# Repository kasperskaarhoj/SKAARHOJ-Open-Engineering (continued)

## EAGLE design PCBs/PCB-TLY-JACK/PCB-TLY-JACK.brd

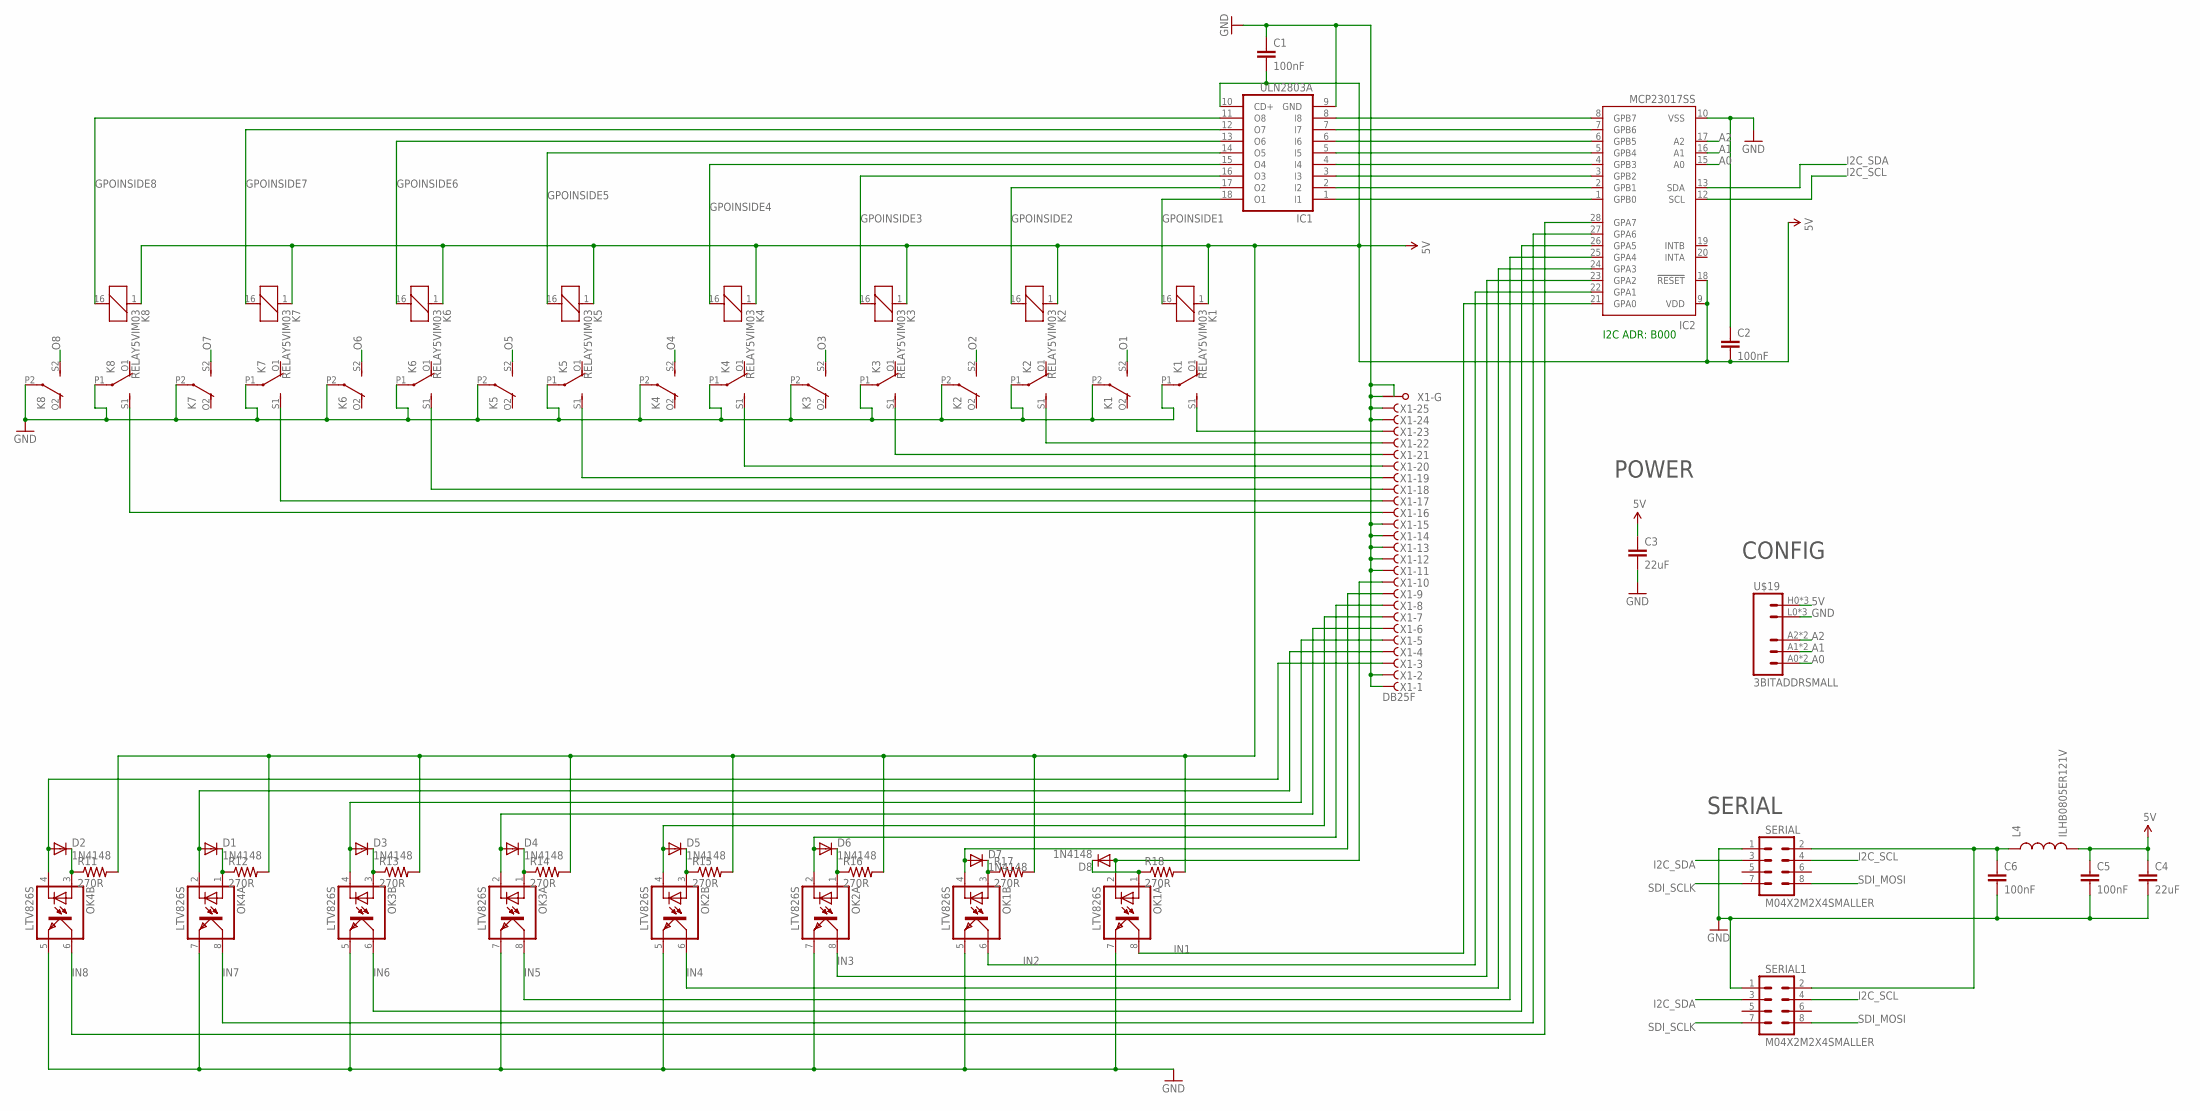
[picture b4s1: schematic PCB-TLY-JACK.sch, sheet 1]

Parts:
C1, C2, C5, C6: 100nF; 0603-CAP
C3, C4: 22uF; 0805
D1, D2, D3, D4, D5, D6, D7, D8: 1N4148; SOD-323
IC1: ULN2803A; SO18W
IC2: MCP23017SS; SSOP28
K1, K2, K3, K4, K5, K6, K7, K8: RELAY5VIM03; DS2Y
L4: ILHB0805ER121V; 0805
OK1, OK2, OK3, OK4: LTV826S; DIL8-SMD
R11, R12, R13, R14, R15, R16, R17, R18: 270R; 0603-RES
SERIAL, SERIAL1: M04X2M2X4SMALLER; M2X4SMALLER
U$19: 3BITADDRSMALL; 3BITADDR_SMALL
X1: DB25F; F25HP

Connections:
5V: C1.2, C2.2, C3.1, C4.1, C5.1, IC1.10 (CD+), IC2.9 (VDD), IC2.18 (!RESET), K1.1, K2.1, K3.1, K4.1, K5.1, K6.1, K7.1, K8.1, L4.2, R11.2, R12.2, R13.2, R14.2, R15.2, R16.2, R17.2, R18.2, U$19.H0 (VCC), U$19.H1 (VCC), U$19.H2 (VCC)
A0: IC2.15 (A0), U$19.A0, U$19.AS0 (A0)
A1: IC2.16 (A1), U$19.A1, U$19.AS1 (A1)
A2: IC2.17 (A2), U$19.A2, U$19.AS2 (A2)
GND: C1.1, C2.1, C3.2, C4.2, C5.2, C6.2, IC1.9 (GND), IC2.10 (VSS), K1.P1, K1.P2, K2.P1, K2.P2, K3.P1, K3.P2, K4.P1, K4.P2, K5.P1, K5.P2, K6.P1, K6.P2, K7.P1, K7.P2, K8.P1, K8.P2, OK1.5 (EMIT), OK1.7 (EMIT), OK2.5 (EMIT), OK2.7 (EMIT), OK3.5 (EMIT), OK3.7 (EMIT), OK4.5 (EMIT), OK4.7 (EMIT), SERIAL.1, SERIAL1.1, U$19.L0 (GND), U$19.L1 (GND), U$19.L2 (GND), X1.1 (F), X1.2 (F), X1.11 (F), X1.12 (F), X1.13 (F), X1.14 (F), X1.15 (F), X1.24 (F), X1.25 (F), X1.G1, X1.G2
GPOINSIDE1: IC1.18 (O1), K1.16 (2)
GPOINSIDE2: IC1.17 (O2), K2.16 (2)
GPOINSIDE3: IC1.16 (O3), K3.16 (2)
GPOINSIDE4: IC1.15 (O4), K4.16 (2)
GPOINSIDE5: IC1.14 (O5), K5.16 (2)
GPOINSIDE6: IC1.13 (O6), K6.16 (2)
GPOINSIDE7: IC1.12 (O7), K7.16 (2)
GPOINSIDE8: IC1.11 (O8), K8.16 (2)
I2C_SCL: IC2.12 (SCL), SERIAL.4, SERIAL1.4
I2C_SDA: IC2.13 (SDA), SERIAL.3, SERIAL1.3
IN1: IC2.21 (GPA0), OK1.8 (COL)
IN2: IC2.22 (GPA1), OK1.6 (COL)
IN3: IC2.23 (GPA2), OK2.8 (COL)
IN4: IC2.24 (GPA3), OK2.6 (COL)
IN5: IC2.25 (GPA4), OK3.8 (COL)
IN6: IC2.26 (GPA5), OK3.6 (COL)
IN7: IC2.27 (GPA6), OK4.8 (COL)
IN8: IC2.28 (GPA7), OK4.6 (COL)
unnamed: K1.S1 (S), X1.23 (F)
unnamed: C6.1, L4.1, SERIAL.2, SERIAL1.2
unnamed: IC1.1 (I1), IC2.1 (GPB0)
unnamed: K2.S1 (S), X1.22 (F)
unnamed: K3.S1 (S), X1.21 (F)
unnamed: D2.1 (C), OK4.3 (A), R11.1
unnamed: K4.S1 (S), X1.20 (F)
unnamed: D1.1 (C), OK4.1 (A), R12.1
unnamed: D3.1 (C), OK3.3 (A), R13.1
unnamed: D4.1 (C), OK3.1 (A), R14.1
unnamed: K5.S1 (S), X1.19 (F)
unnamed: D5.1 (C), OK2.3 (A), R15.1
unnamed: D6.1 (C), OK2.1 (A), R16.1
unnamed: D7.1 (C), OK1.3 (A), R17.1
unnamed: K6.S1 (S), X1.18 (F)
unnamed: D8.1 (C), OK1.1 (A), R18.1
unnamed: K7.S1 (S), X1.17 (F)
unnamed: K8.S1 (S), X1.16 (F)
unnamed: IC1.2 (I2), IC2.2 (GPB1)
unnamed: IC1.3 (I3), IC2.3 (GPB2)
unnamed: IC1.4 (I4), IC2.4 (GPB3)
unnamed: IC1.5 (I5), IC2.5 (GPB4)
unnamed: IC1.6 (I6), IC2.6 (GPB5)
unnamed: IC1.7 (I7), IC2.7 (GPB6)
unnamed: IC1.8 (I8), IC2.8 (GPB7)
unnamed: D8.2 (A), OK1.2 (C), X1.10 (F)
unnamed: D4.2 (A), OK3.2 (C), X1.6 (F)
unnamed: D7.2 (A), OK1.4 (C), X1.9 (F)
unnamed: D6.2 (A), OK2.2 (C), X1.8 (F)
unnamed: D5.2 (A), OK2.4 (C), X1.7 (F)
unnamed: D3.2 (A), OK3.4 (C), X1.5 (F)
unnamed: D1.2 (A), OK4.2 (C), X1.4 (F)
unnamed: D2.2 (A), OK4.4 (C), X1.3 (F)
O1: K1.S2 (S)
O2: K2.S2 (S)
O3: K3.S2 (S)
O4: K4.S2 (S)
O5: K5.S2 (S)
O6: K6.S2 (S)
O7: K7.S2 (S)
O8: K8.S2 (S)
SDI_MOSI: SERIAL.8, SERIAL1.8
SDI_SCLK: SERIAL.7, SERIAL1.7

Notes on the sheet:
I2C ADR: B000
SERIAL
POWER
CONFIG

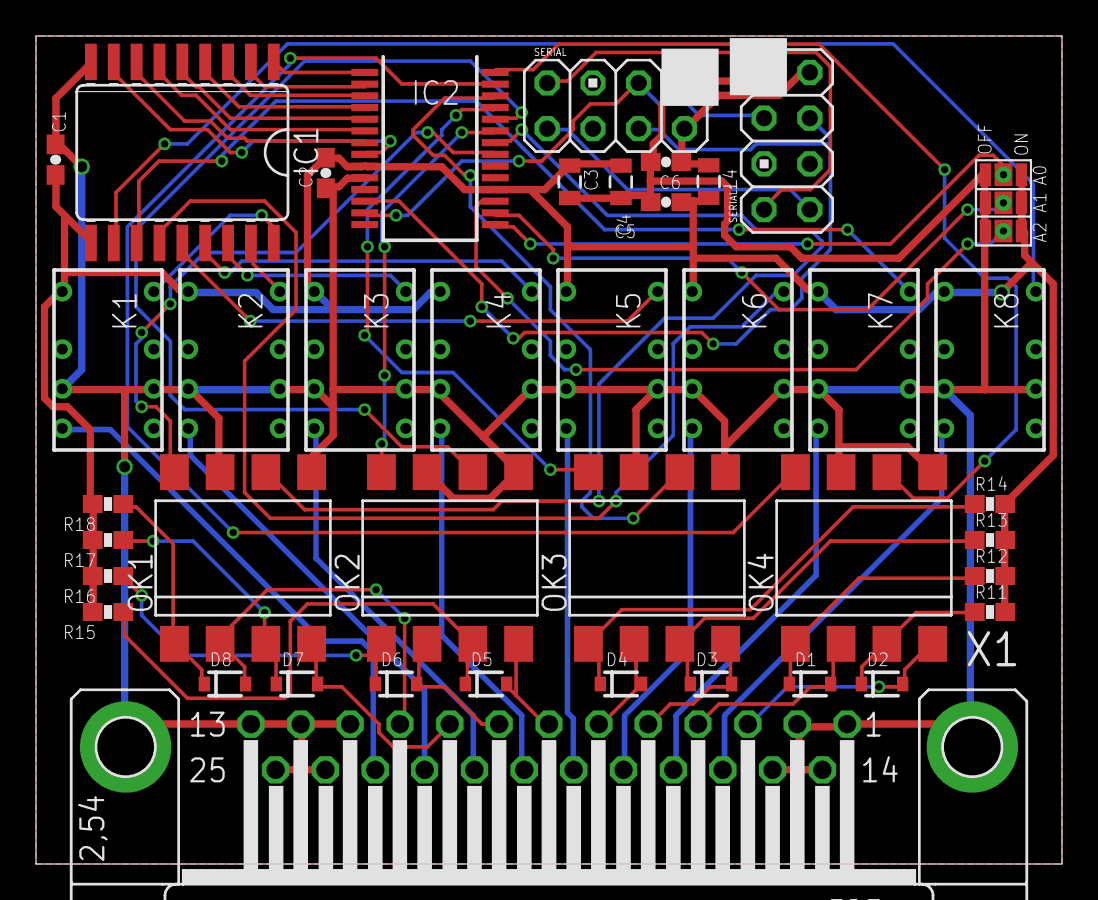
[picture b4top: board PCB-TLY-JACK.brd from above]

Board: 2 copper layers, 57.0 x 46.0 mm, 41 parts (0 on the bottom side), 58 nets.

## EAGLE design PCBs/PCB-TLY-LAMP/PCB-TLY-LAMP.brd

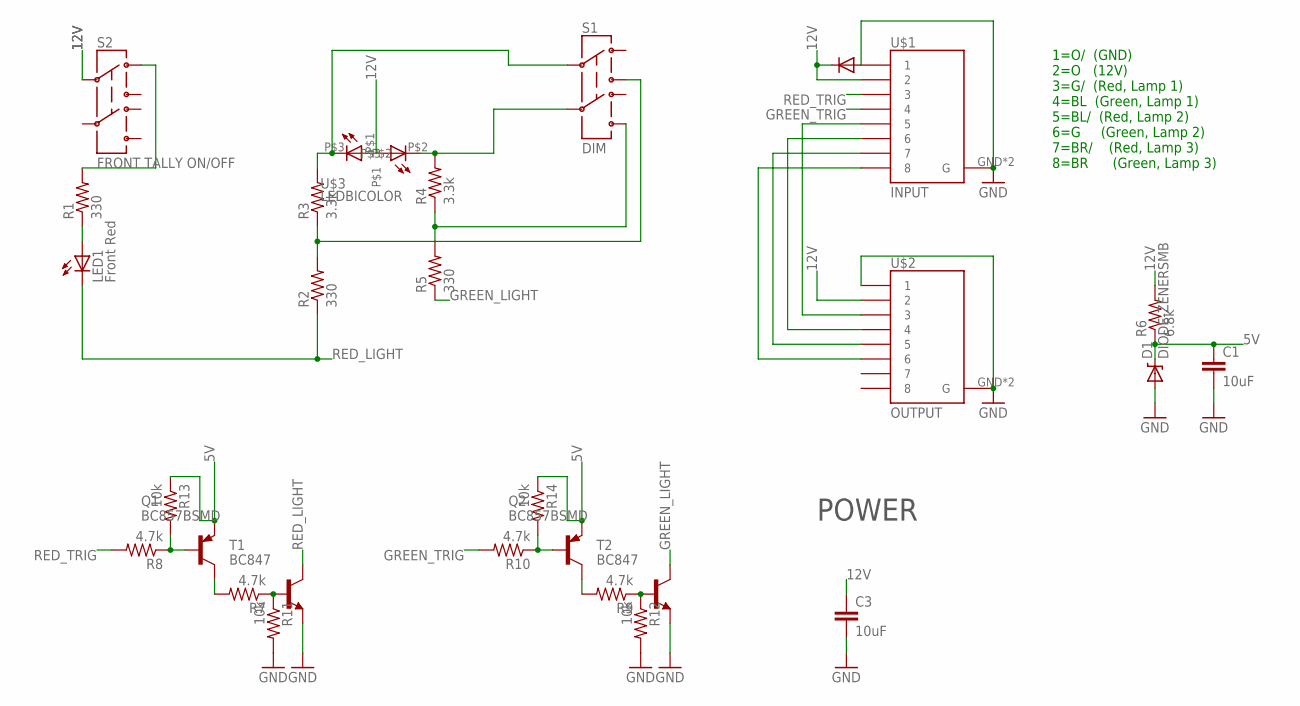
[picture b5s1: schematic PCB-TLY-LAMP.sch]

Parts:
C1, C3: 10uF; 0805
D1: DIODE-ZENERSMB; SMB-DIODE
LED1: Front Red; LED20
Q1, Q2: BC857BSMD; SOT23-BEC
R1, R2, R5: 330; 0603-RES
R3, R4: 3.3k; 0603-RES
R6: 6.8k; 0603-RES
R7, R8, R9, R10: 4.7k; 0603-RES
R11, R12, R13, R14: 10k; 0603-RES
S1: DIM; TECONNECTIVITY-DPDT
S2: FRONT TALLY ON/OFF; TECONNECTIVITY-DPDT
T1, T2: BC847; SOT23
U$1: INPUT; RJ45-8_GND
U$2: OUTPUT; RJ45-8_GND
U$3: LEDBICOLOR

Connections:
5V: C1.1, D1.C, Q1.E, Q2.E, R6.1, R13.1, R14.1
12V: C3.1, R6.2, S2.P$2 (2), U$1.2, U$2.2, U$3.P$1
GND: C1.2, C3.2, D1.A, R11.2, R12.2, T1.2 (E), T2.2 (E), U$1.1, U$1.GND (G), U$1.GND1 (G), U$2.1, U$2.GND (G), U$2.GND1 (G)
GREEN_LIGHT: R5.1, T2.3 (C)
GREEN_TRIG: R10.2, U$1.4
unnamed: R1.2, S2.P$1 (1)
unnamed: LED1.P$1 (A), R1.1
unnamed: R2.2, R3.1, S1.P$3 (3)
unnamed: R4.1, R5.2, S1.P$6 (6)
unnamed: R4.2, S1.P$5 (5), U$3.P$2
unnamed: R3.2, S1.P$2 (2), U$3.P$3
unnamed: U$1.5, U$2.3
unnamed: U$1.6, U$2.4
unnamed: R7.1, R11.1, T1.1 (B)
unnamed: Q1.C, R7.2
unnamed: U$1.7, U$2.5
unnamed: U$1.8, U$2.6
unnamed: R9.1, R12.1, T2.1 (B)
unnamed: Q2.C, R9.2
unnamed: Q2.B, R10.1, R14.2
unnamed: Q1.B, R8.1, R13.2
RED_LIGHT: LED1.P$2 (C), R2.1, T1.3 (C)
RED_TRIG: R8.2, U$1.3

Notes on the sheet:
POWER
1=O/ (GND) 2=O (12V) 3=G/ (Red, Lamp 1) 4=BL (Green, Lamp 1) 5=BL/ (Red, Lamp 2) 6=G (Green, Lamp 2) 7=BR/ (Red, Lamp 3) 8=BR (Green, Lamp 3)

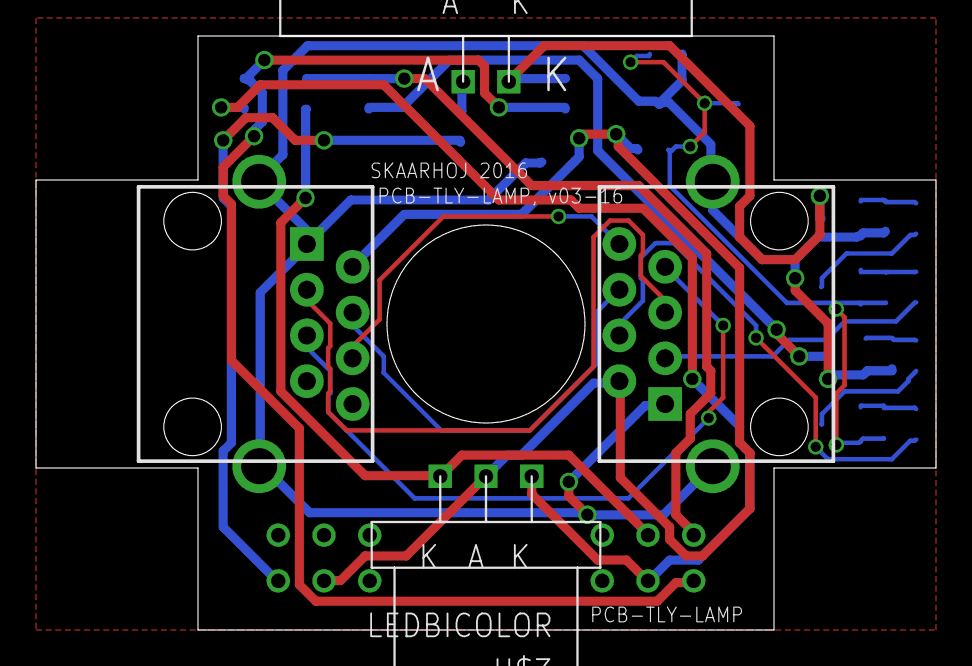
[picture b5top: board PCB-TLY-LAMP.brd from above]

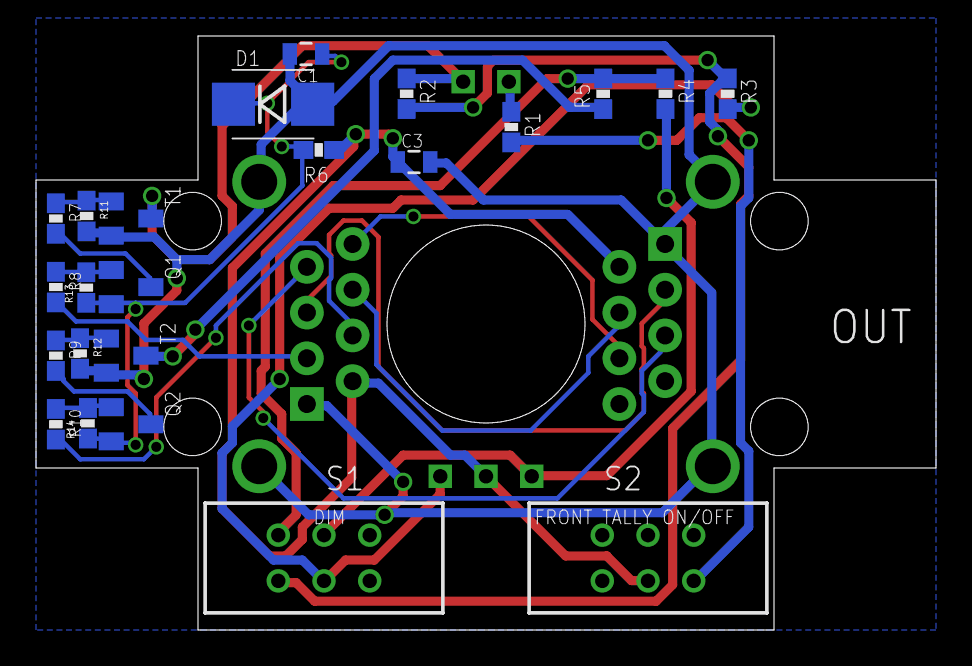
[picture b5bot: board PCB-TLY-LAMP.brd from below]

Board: 2 copper layers, 50.0 x 33.0 mm, 27 parts (23 on the bottom side), 23 nets.

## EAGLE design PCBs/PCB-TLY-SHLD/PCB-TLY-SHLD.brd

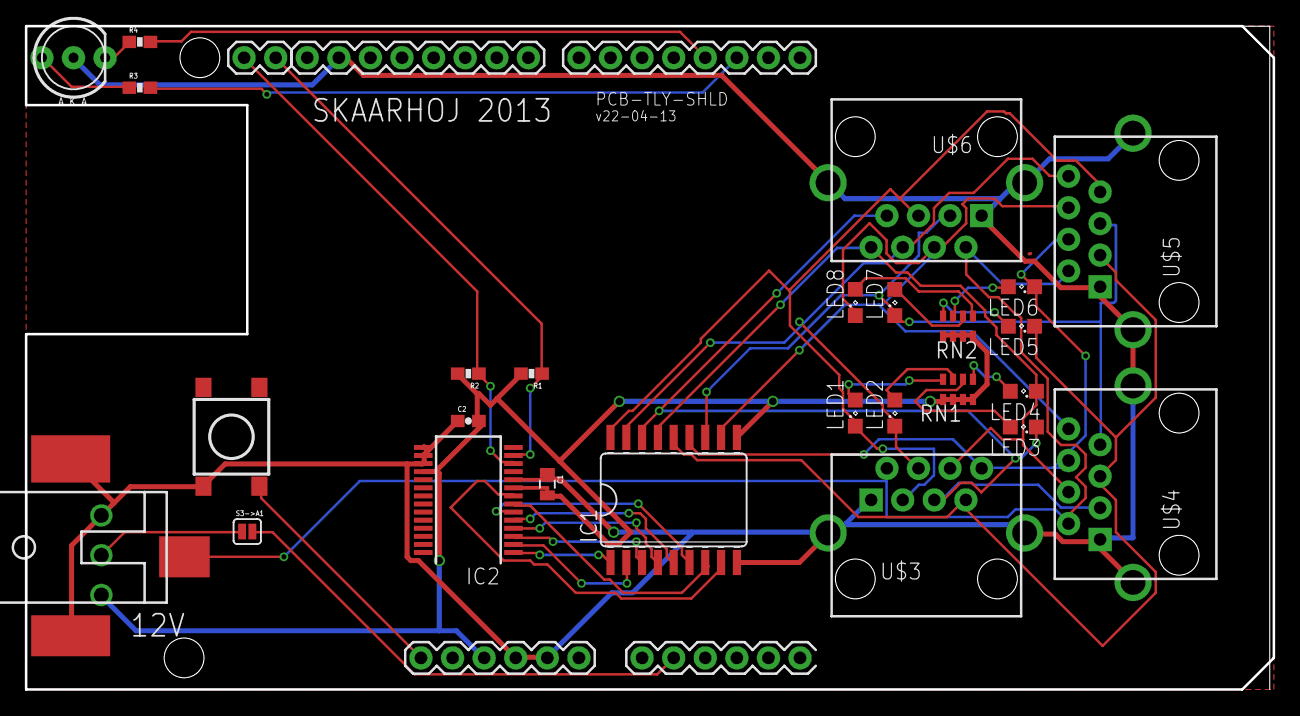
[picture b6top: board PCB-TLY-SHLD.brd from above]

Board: 2 copper layers, 100.3 x 53.3 mm, 29 parts (1 on the bottom side), 36 nets.

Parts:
C1: 100nF; 0805
C2: 100nF; 0603-CAP
GND: ARDUINO_SHIELD; ARDUINO_BOXSHIELD_NOHOLES
IC1: ULN2803A; SO18W
IC2: MCP23017SS; SSOP28
J1: POWER_JACK_SMD
JP4: 1X02
LED1, LED2, LED3, LED4, LED5, LED6, LED7, LED8: SML0805
R1, R2: 1K5; 0603-RES
R3, R4: 270; 0603-RES
RN1, RN2: 220; CAY16_HAND
S1: SWITCH-MOMENTARY-2; TACTILE_SWITCH_TALL
S3: CFG; TECONNECTIVITY-DPST
S3->A1: SOLDERJUMPERNC; SJ_2S
U$3: Tally 1-2-3; RJ45-8_GND
U$4: Tally 2-3-4; RJ45-8_GND
U$5: Tally 3-4-1; RJ45-8_GND
U$6: Tally 4-1-2; RJ45-8_GND
U$7: LEDBICOLOR-AKA; LED5MM-BICOLOR

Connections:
5V: C1.2, C2.2, GND.5V@0, IC1.10, IC2.9, IC2.18, R1.2, R2.2, RN1.1, RN1.2, RN1.3, RN1.4, RN2.1, RN2.2, RN2.3, RN2.4, S3.P$1
A1CFG: GND.A1, S3->A1.2
D2: GND.2, R3.2
D3: GND.3, R4.2
GND: C1.1, C2.1, GND.GND@0, GND.GND@1, GND.GND@4, IC1.9, IC2.10, IC2.15, IC2.16, IC2.17, J1.GND, J1.SHUNT, S1.A2, S3.P$3, U$3.1, U$3.GND, U$3.GND1, U$4.1, U$4.GND, U$4.GND1, U$5.1, U$5.GND, U$5.GND1, U$6.1, U$6.GND, U$6.GND1, U$7.K1
I2C_SCL: IC2.12, JP4.2, R2.1
I2C_SDA: IC2.13, JP4.1, R1.1
unnamed: IC1.18, LED1.C, U$3.3, U$5.7, U$6.5
unnamed: S3.P$2, S3->A1.1
unnamed: J1.PWR, U$3.2, U$4.2, U$5.2, U$6.2
unnamed: IC1.1, IC2.1
unnamed: IC1.17, LED2.C, U$3.4, U$5.8, U$6.6
unnamed: R4.1, U$7.A2
unnamed: R3.1, U$7.A3
unnamed: IC1.16, LED3.C, U$3.5, U$4.3, U$6.7
unnamed: IC1.15, LED4.C, U$3.6, U$4.4, U$6.8
unnamed: IC1.14, LED5.C, U$3.7, U$4.5, U$5.3
unnamed: IC1.13, LED6.C, U$3.8, U$4.6, U$5.4
unnamed: IC1.12, LED7.C, U$4.7, U$5.5, U$6.3
unnamed: IC1.11, LED8.C, U$4.8, U$5.6, U$6.4
unnamed: IC1.2, IC2.2
unnamed: IC1.3, IC2.3
unnamed: IC1.4, IC2.4
unnamed: IC1.5, IC2.5
unnamed: IC1.6, IC2.6
unnamed: IC1.7, IC2.7
unnamed: IC1.8, IC2.8
unnamed: LED1.A, RN1.8
unnamed: LED2.A, RN1.7
unnamed: LED3.A, RN1.6
unnamed: LED4.A, RN1.5
unnamed: LED5.A, RN2.8
unnamed: LED6.A, RN2.7
unnamed: LED7.A, RN2.6
unnamed: LED8.A, RN2.5
RES: GND.RESET, S1.B2

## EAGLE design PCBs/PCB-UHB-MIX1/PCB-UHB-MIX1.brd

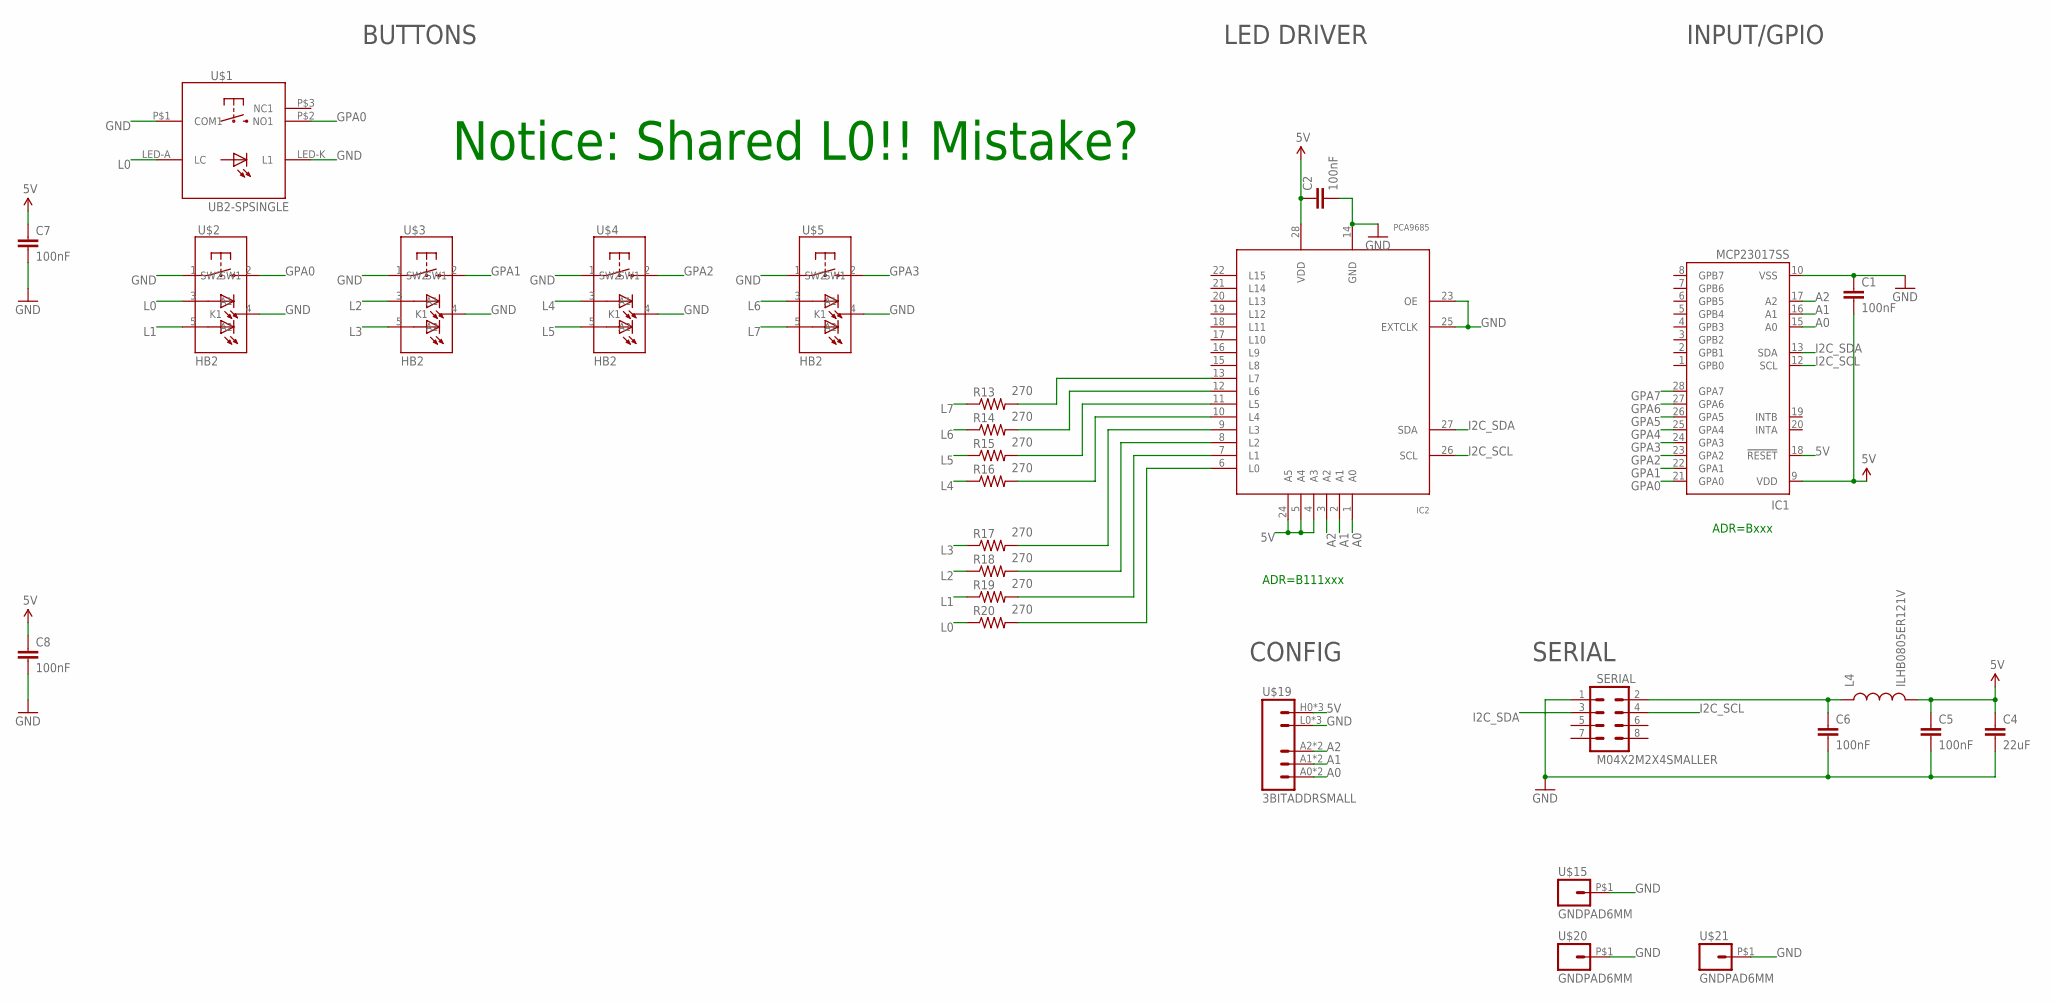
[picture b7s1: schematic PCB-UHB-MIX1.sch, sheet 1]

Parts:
C1, C2, C5, C6, C7, C8: 100nF; 0603-CAP
C4: 22uF; 0805
IC1: MCP23017SS; SSOP28; MPN MCP23017-E/SS
IC2: PCA9685; TSSOP28
L4: ILHB0805ER121V; 0805
R13, R14, R15, R16, R17, R18, R19, R20: 270; 0603-RES
SERIAL: M04X2M2X4SMALLER; M2X4SMALLER
U$1: UB2-SPSINGLE
U$2, U$3, U$4, U$5: HB2
U$15, U$20, U$21: GNDPAD6MM; 3.2MMPAD6MM
U$19: 3BITADDRSMALL; 3BITADDR_SMALL

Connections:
5V: C1.2, C2.1, C4.1, C5.1, C7.1, C8.1, IC1.9 (VDD), IC1.18 (!RESET), IC2.4 (A3), IC2.5 (A4), IC2.24 (A5), IC2.28 (VDD), L4.2, U$19.H0 (VCC), U$19.H1 (VCC), U$19.H2 (VCC)
A0: IC1.15 (A0), IC2.1 (A0), U$19.A0, U$19.AS0 (A0)
A1: IC1.16 (A1), IC2.2 (A1), U$19.A1, U$19.AS1 (A1)
A2: IC1.17 (A2), IC2.3 (A2), U$19.A2, U$19.AS2 (A2)
GND: C1.1, C2.2, C4.2, C5.2, C6.2, C7.2, C8.2, IC1.10 (VSS), IC2.14 (GND), IC2.23 (OE), IC2.25 (EXTCLK), SERIAL.1, U$1.LED-K (L1), U$1.P$1 (COM1), U$2.1 (SW1), U$2.4 (K1), U$3.1 (SW1), U$3.4 (K1), U$4.1 (SW1), U$4.4 (K1), U$5.1 (SW1), U$5.4 (K1), U$15.P$1, U$19.L0 (GND), U$19.L1 (GND), U$19.L2 (GND), U$20.P$1, U$21.P$1
GPA0: IC1.21 (GPA0), U$1.P$2 (NO1), U$2.2 (SW2)
GPA1: IC1.22 (GPA1), U$3.2 (SW2)
GPA2: IC1.23 (GPA2), U$4.2 (SW2)
GPA3: IC1.24 (GPA3), U$5.2 (SW2)
GPA4: IC1.25 (GPA4)
GPA5: IC1.26 (GPA5)
GPA6: IC1.27 (GPA6)
GPA7: IC1.28 (GPA7)
I2C_SCL: IC1.12 (SCL), IC2.26 (SCL), SERIAL.4
I2C_SDA: IC1.13 (SDA), IC2.27 (SDA), SERIAL.3
L0: R20.1, U$1.LED-A (LC), U$2.3 (A1)
L1: R19.1, U$2.5 (A2)
L2: R18.1, U$3.3 (A1)
L3: R17.1, U$3.5 (A2)
L4: R16.1, U$4.3 (A1)
L5: R15.1, U$4.5 (A2)
L6: R14.1, U$5.3 (A1)
L7: R13.1, U$5.5 (A2)
unnamed: C6.1, L4.1, SERIAL.2
unnamed: IC2.13 (L7), R13.2
unnamed: IC2.12 (L6), R14.2
unnamed: IC2.11 (L5), R15.2
unnamed: IC2.10 (L4), R16.2
unnamed: IC2.9 (L3), R17.2
unnamed: IC2.8 (L2), R18.2
unnamed: IC2.7 (L1), R19.2
unnamed: IC2.6 (L0), R20.2

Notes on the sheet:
ADR=B111xxx
ADR=Bxxx
BUTTONS
LED DRIVER
INPUT/GPIO
SERIAL
CONFIG
Notice: Shared L0!! Mistake?

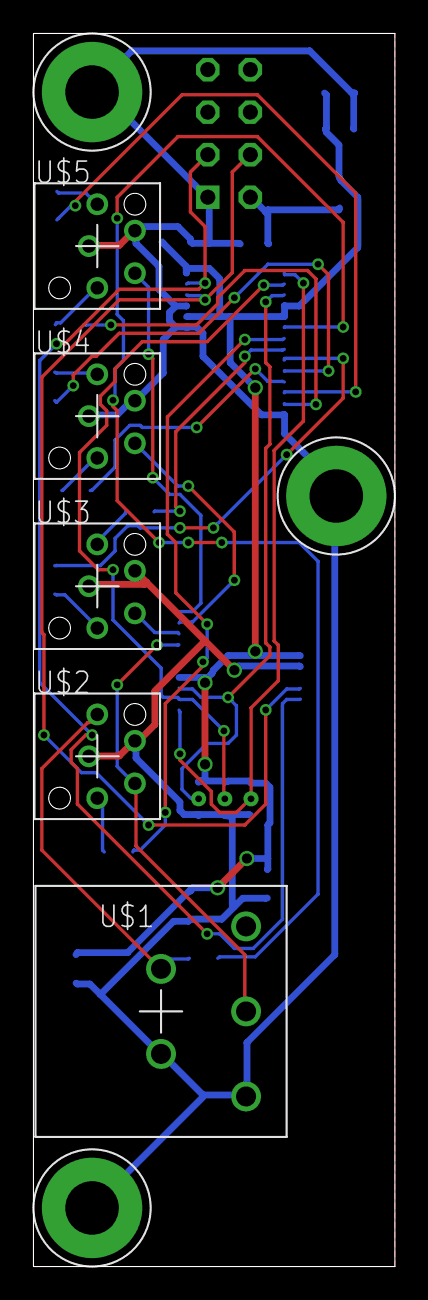
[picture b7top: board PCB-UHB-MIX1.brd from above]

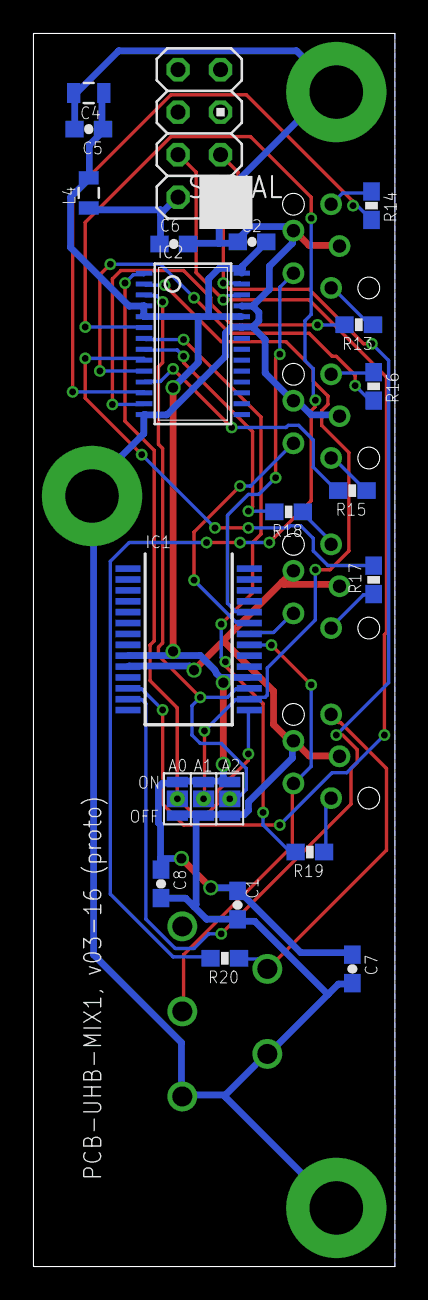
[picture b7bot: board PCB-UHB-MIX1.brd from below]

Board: 2 copper layers, 21.6 x 73.7 mm, 28 parts (20 on the bottom side), 28 nets.

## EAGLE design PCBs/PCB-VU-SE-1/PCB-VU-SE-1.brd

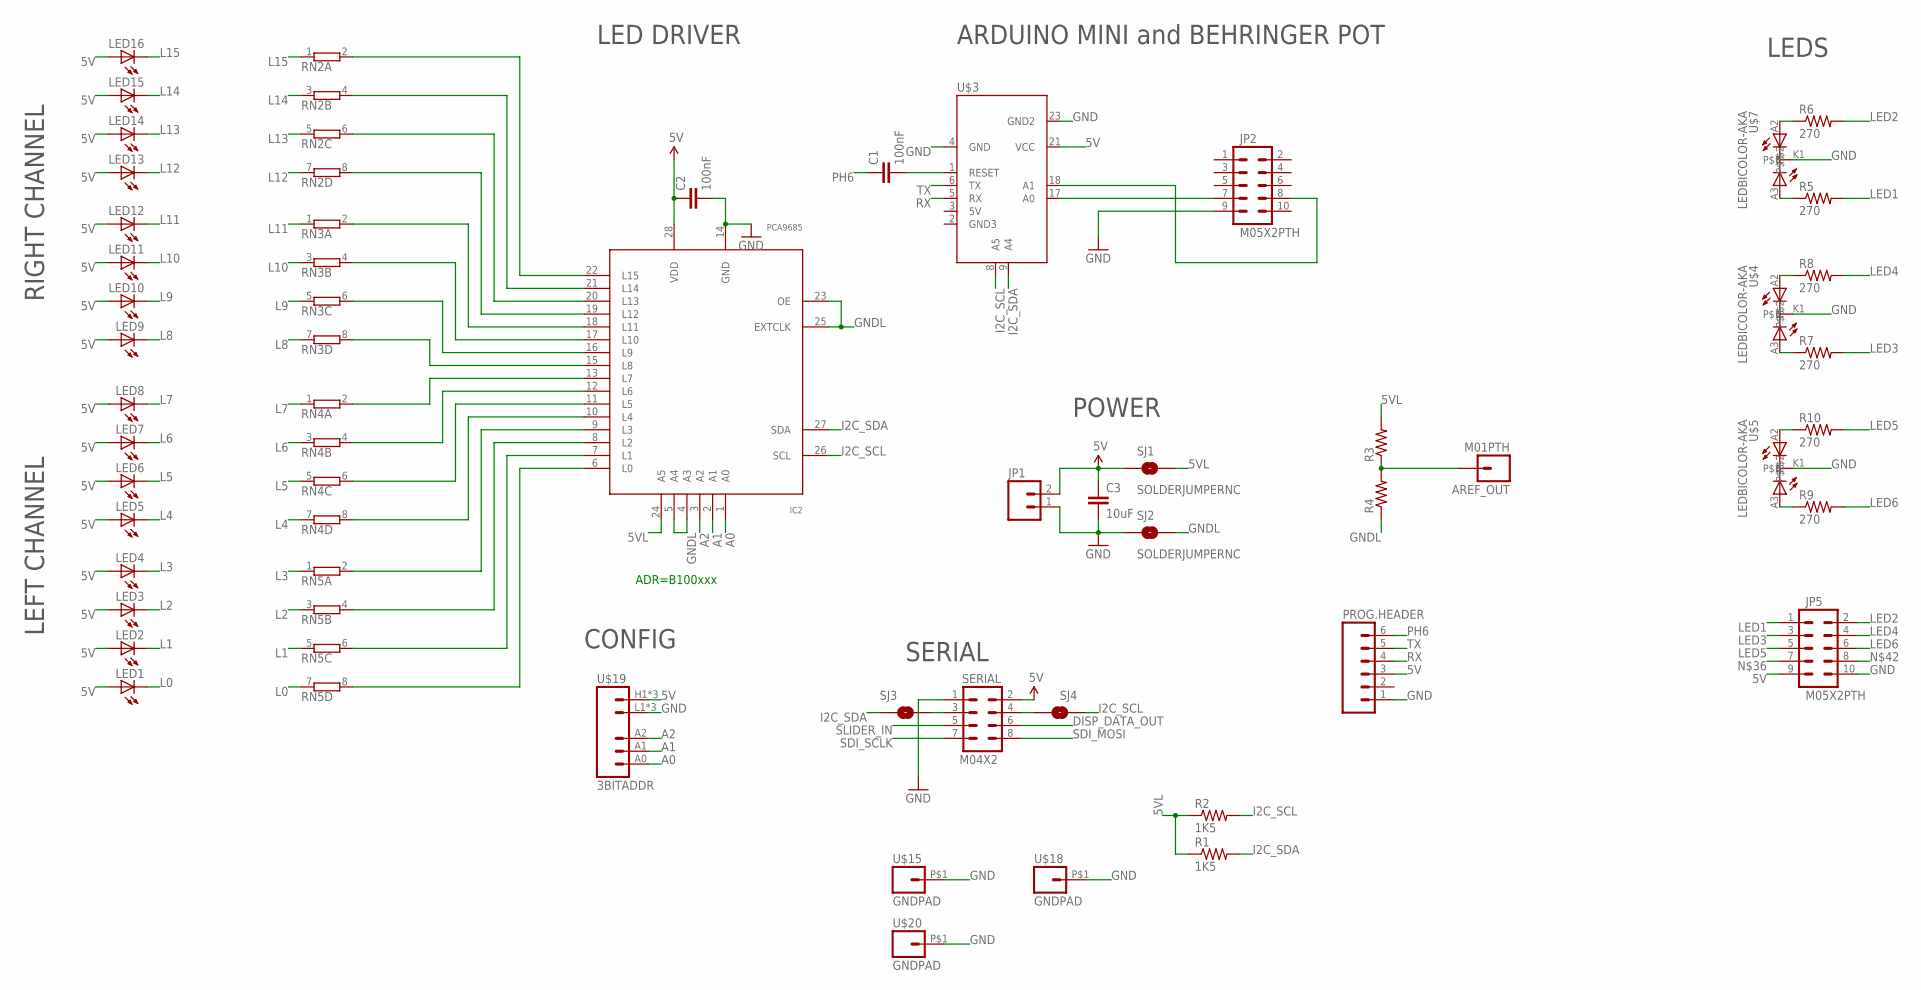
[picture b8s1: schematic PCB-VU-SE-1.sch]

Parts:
AREF_OUT: M01PTH; 1X01
C1, C2: 100nF; 0603-CAP
C3: 10uF; 0805
IC2: PCA9685; TSSOP28
JP1: M02PTH; 1X02
JP2, JP5: M05X2PTH; AVR_ICSP
LED1, LED2, LED3, LED4, LED5, LED6, LED7, LED8, LED9, LED10, LED11, LED12, LED13, LED14, LED15, LED16: LED3MM
PROG.HEADER: M06LOCK; 1X06_LOCK
R1, R2: 1K5; 0603-RES
R3, R4: RESISTOR0603-RES; 0603-RES
R5, R6, R7, R8, R9, R10: 270; 0603-RES
RN2, RN3, RN4, RN5: E4R; SIL8
SERIAL: M04X2; 2X4
SJ1, SJ2, SJ3, SJ4: SOLDERJUMPERNC; SJ_2S
U$3: ARDUINO_MINI_SE1
U$4, U$5, U$7: LEDBICOLOR-AKA; LED5MM-BICOLOR
U$15, U$18, U$20: GNDPAD; 3.2MMPAD
U$19: 3BITADDR

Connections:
A0: IC2.1 (A0), U$19.A0
A1: IC2.2 (A1), U$19.A1
A2: IC2.3 (A2), U$19.A2
AREF: AREF_OUT.1, R3.1, R4.2
DISP_DATA_OUT: SERIAL.6
I2C_SCL: IC2.26 (SCL), R2.2, SJ4.2, U$3.8 (A5)
I2C_SDA: IC2.27 (SDA), R1.2, SJ3.1, U$3.9 (A4)
L0: LED1.K (C), RN5.7 (1)
L1: LED2.K (C), RN5.5 (1)
L2: LED3.K (C), RN5.3 (1)
L3: LED4.K (C), RN5.1
L4: LED5.K (C), RN4.7 (1)
L5: LED6.K (C), RN4.5 (1)
L6: LED7.K (C), RN4.3 (1)
L7: LED8.K (C), RN4.1
L8: LED9.K (C), RN3.7 (1)
L9: LED10.K (C), RN3.5 (1)
L10: LED11.K (C), RN3.3 (1)
L11: LED12.K (C), RN3.1
L12: LED13.K (C), RN2.7 (1)
L13: LED14.K (C), RN2.5 (1)
L14: LED15.K (C), RN2.3 (1)
L15: LED16.K (C), RN2.1
LED1: JP5.1, R5.2
LED2: JP5.2, R6.2
LED3: JP5.3, R7.2
LED4: JP5.4, R8.2
LED5: JP5.5, R10.2
LED6: JP5.6, R9.2
unnamed: SERIAL.3, SJ3.2
unnamed: IC2.13 (L7), RN4.2
unnamed: IC2.12 (L6), RN4.4 (2)
unnamed: SERIAL.4, SJ4.1
unnamed: IC2.11 (L5), RN4.6 (2)
unnamed: IC2.10 (L4), RN4.8 (2)
unnamed: IC2.9 (L3), RN5.2
unnamed: IC2.8 (L2), RN5.4 (2)
unnamed: IC2.7 (L1), RN5.6 (2)
unnamed: JP2.8, U$3.18 (A1)
unnamed: JP2.7, U$3.17 (A0)
unnamed 40: R6.1, U$7.A2; also elsewhere on the board
unnamed: IC2.6 (L0), RN5.8 (2)
unnamed: IC2.15 (L8), RN3.8 (2)
unnamed: IC2.16 (L9), RN3.6 (2)
unnamed: IC2.17 (L10), RN3.4 (2)
unnamed: IC2.18 (L11), RN3.2
unnamed: IC2.19 (L12), RN2.8 (2)
unnamed: IC2.20 (L13), RN2.6 (2)
unnamed: IC2.21 (L14), RN2.4 (2)
unnamed: IC2.22 (L15), RN2.2
unnamed 50: R5.1, U$7.A3; also elsewhere on the board
unnamed 51: R8.1, U$4.A2; also elsewhere on the board
unnamed 52: R7.1, U$4.A3; also elsewhere on the board
unnamed 53: R10.1, U$5.A2; also elsewhere on the board
unnamed 54: R9.1, U$5.A3; also elsewhere on the board
unnamed: C1.2, U$3.1 (RESET)
PH6: C1.1, PROG.HEADER.6
RX: PROG.HEADER.4, U$3.5 (RX)
SDI_MOSI: SERIAL.8
SDI_SCLK: SERIAL.7
SLIDER_IN: SERIAL.5
TX: PROG.HEADER.5, U$3.6 (TX)

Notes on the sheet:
ADR=B100xxx
LED DRIVER
POWER
SERIAL
ARDUINO MINI and BEHRINGER POT
LEFT CHANNEL
RIGHT CHANNEL
LEDS
CONFIG

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
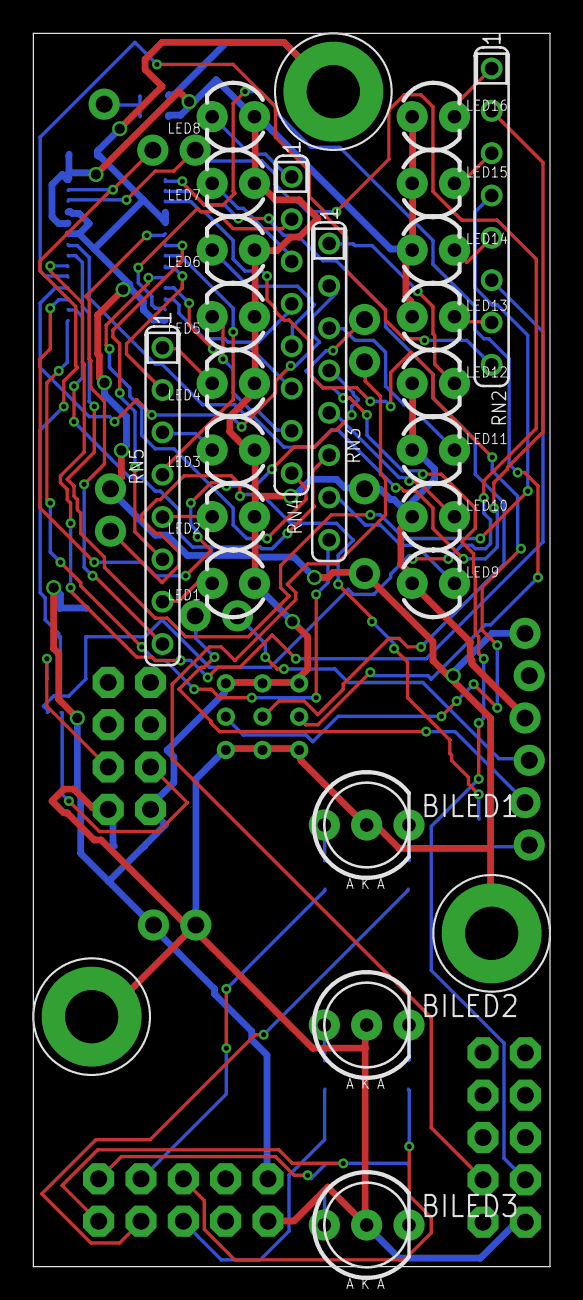
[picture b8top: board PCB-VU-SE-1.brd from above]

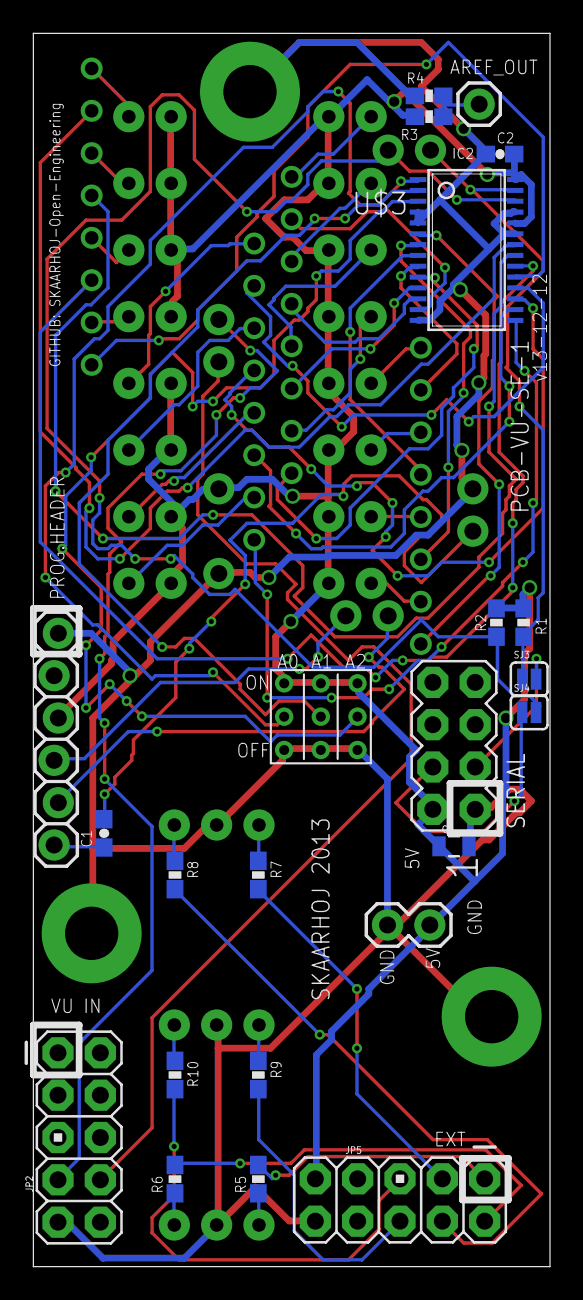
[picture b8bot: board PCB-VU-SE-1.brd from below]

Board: 2 copper layers, 31.0 x 74.0 mm, 50 parts (24 on the bottom side), 60 nets.

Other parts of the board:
BILED1, BILED2, BILED3: LEDBICOLOR-AKA; LED5MM-BICOLOR

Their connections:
unnamed 40: BILED3.A2; also elsewhere on the board
unnamed 50: BILED3.A3; also elsewhere on the board
unnamed 51: BILED1.A2; also elsewhere on the board
unnamed 52: BILED1.A3; also elsewhere on the board
unnamed 53: BILED2.A2; also elsewhere on the board
unnamed 54: BILED2.A3; also elsewhere on the board
